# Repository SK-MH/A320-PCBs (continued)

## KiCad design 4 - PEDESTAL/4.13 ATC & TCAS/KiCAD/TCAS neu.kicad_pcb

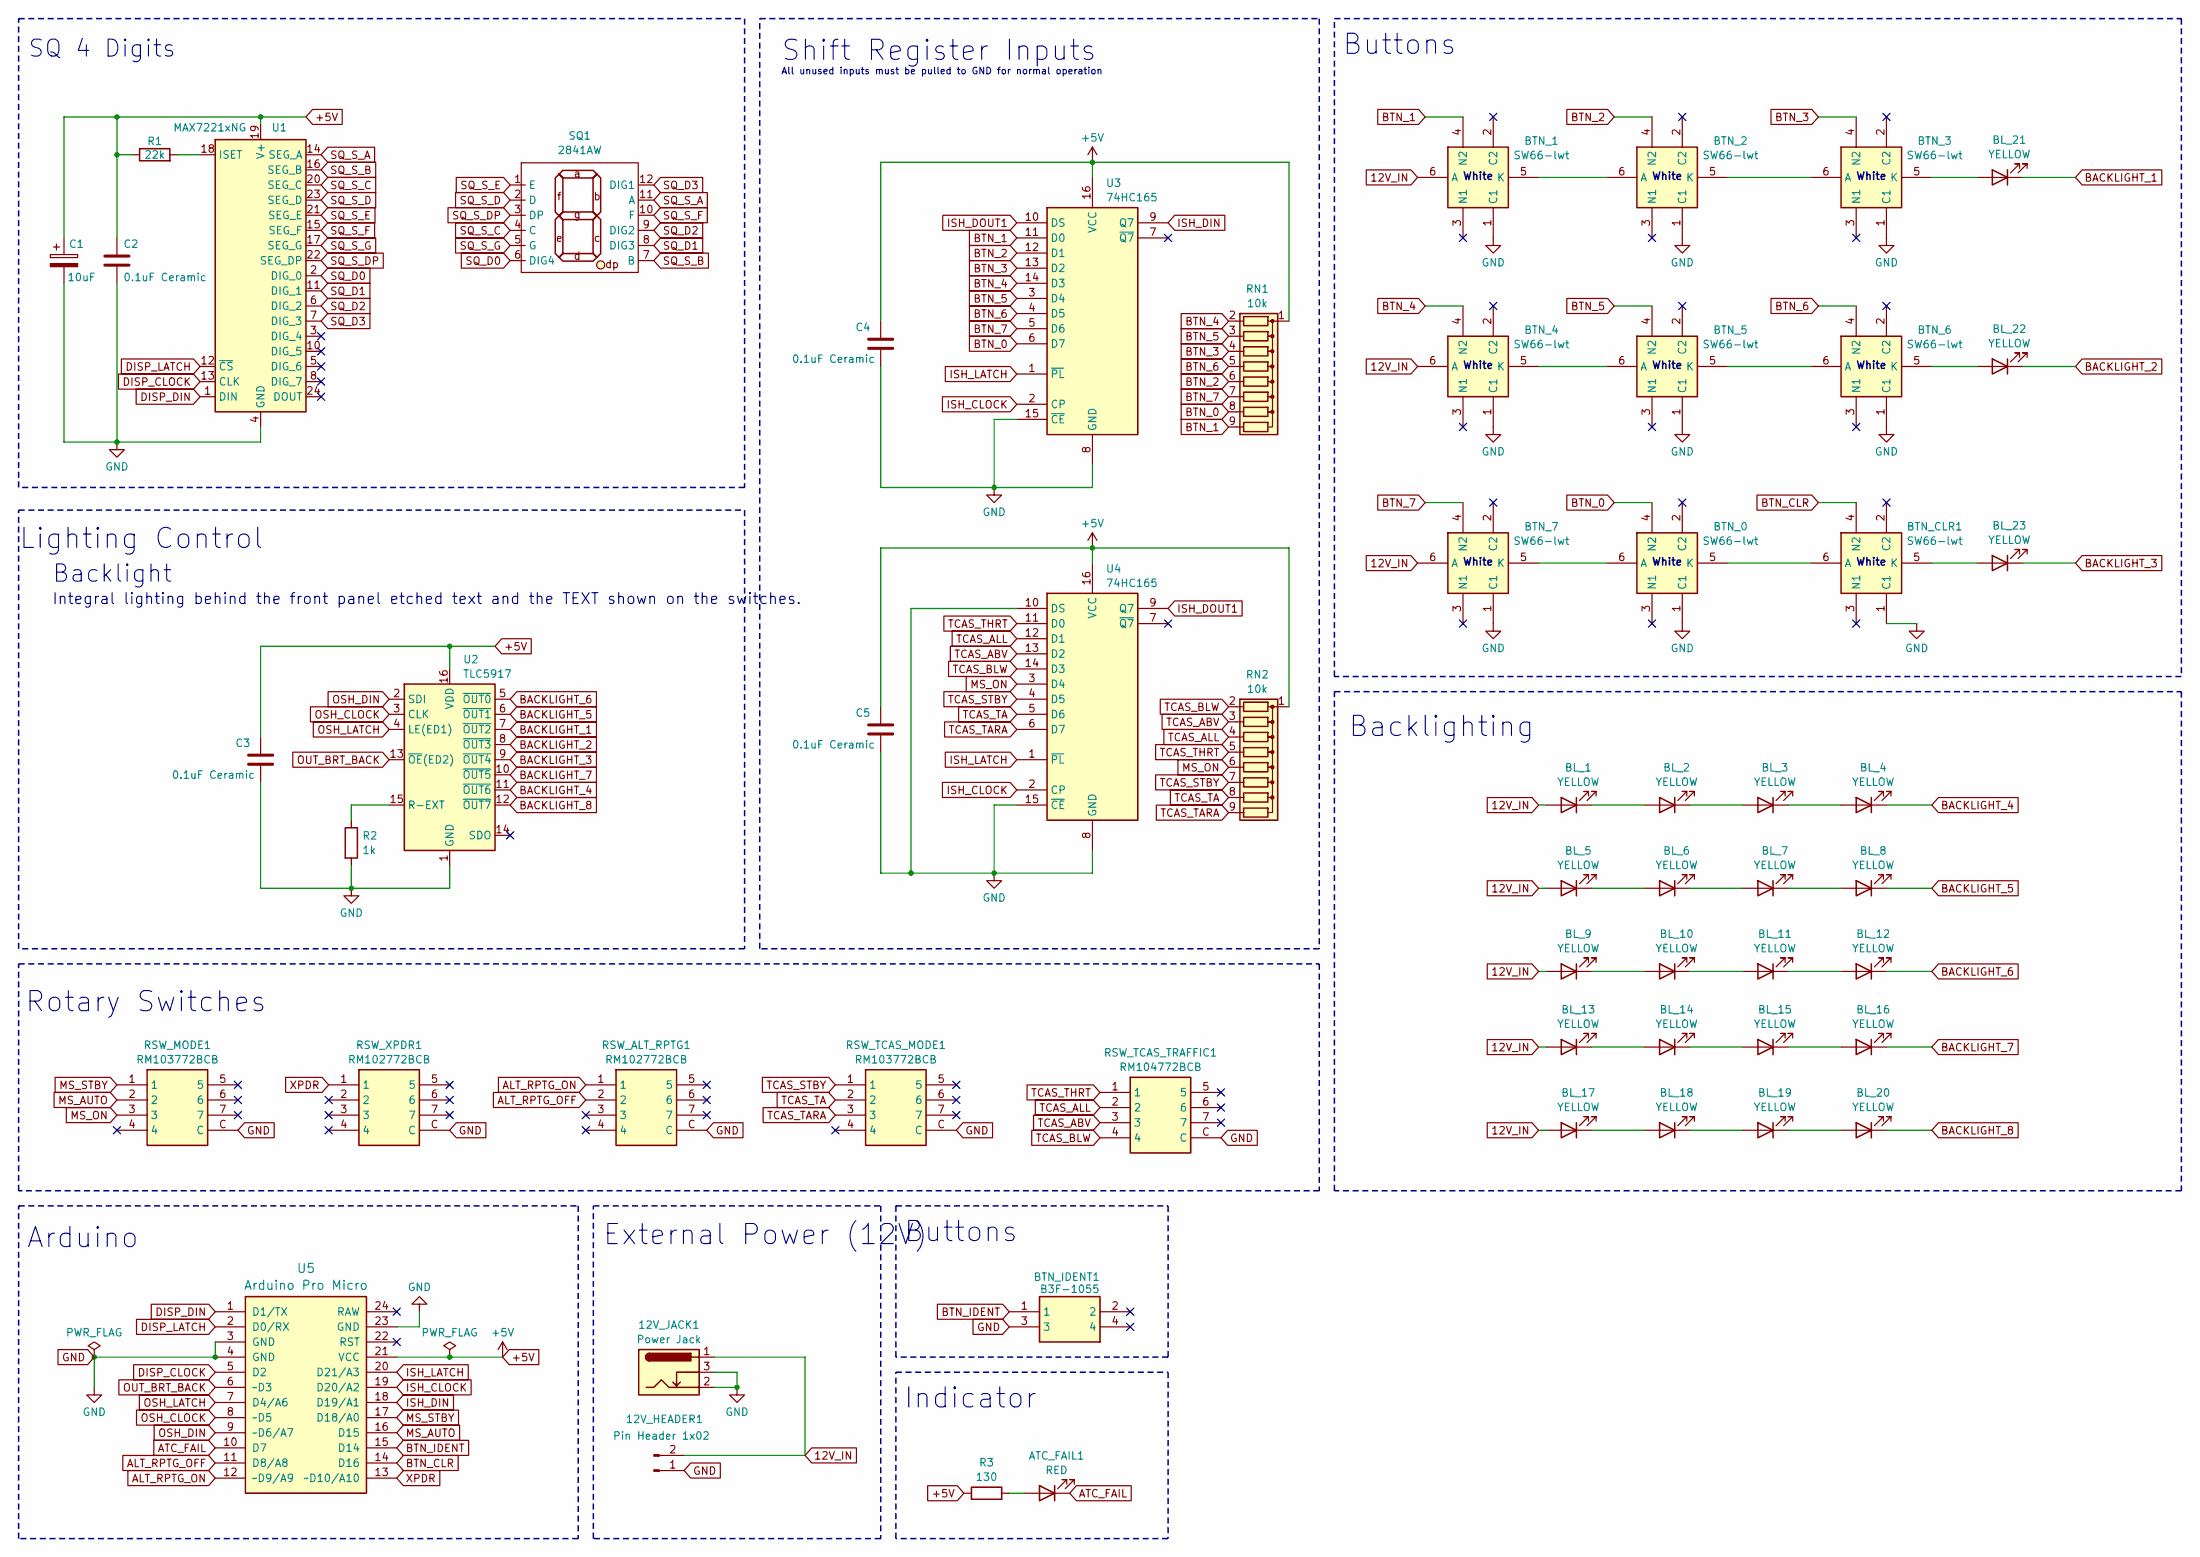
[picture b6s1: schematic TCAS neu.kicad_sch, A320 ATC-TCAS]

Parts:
12V_HEADER1: Pin Header 1x02; JST_EH_B2B-EH-A_1x02_P2.50mm_Vertical
12V_JACK1: Power Jack; BarrelJack_Horizontal
ATC_FAIL1: RED; LED_D3.0mm
BL_1, BL_2, BL_3, BL_4, BL_5, BL_6, BL_7, BL_8, BL_9, BL_10, BL_11, BL_12, BL_13, BL_14, BL_15, BL_16, BL_17, BL_18, BL_19, BL_20, BL_21, BL_22, BL_23: YELLOW; LED_D3.0mm
BTN_0, BTN_1, BTN_2, BTN_3, BTN_4, BTN_5, BTN_6, BTN_7: SW66-lwt
BTN_CLR1: SW66-lwt
BTN_IDENT1: B3F-1055; B3F1000; Mouser Part Number 653-B3F-1055
C1: 10uF; CP_Radial_D4.0mm_P1.50mm
C2, C3, C4, C5: 0.1uF Ceramic; C_Disc_D3.0mm_W1.6mm_P2.50mm
R1: 22k; R_Axial_DIN0204_L3.6mm_D1.6mm_P7.62mm_Horizontal
R2: 1k; R_Axial_DIN0204_L3.6mm_D1.6mm_P7.62mm_Horizontal
R3: 130; R_Axial_DIN0204_L3.6mm_D1.6mm_P7.62mm_Horizontal
RN1, RN2: 10k; R_Array_SIP9
RSW_ALT_RPTG1: RM102772BCB; myRM103772BCB; Mouser Part Number 611-RM103772BCB
RSW_MODE1: RM103772BCB; myRM103772BCB; Mouser Part Number 611-RM103772BCB
RSW_TCAS_MODE1: RM103772BCB; myRM103772BCB; Mouser Part Number 611-RM103772BCB
RSW_TCAS_TRAFFIC1: RM104772BCB; myRM103772BCB; Mouser Part Number 611-RM103772BCB
RSW_XPDR1: RM102772BCB; myRM103772BCB; Mouser Part Number 611-RM103772BCB
SQ1: 2841AW
U1: MAX7221xNG; DIP-24_W7.62mm
U2: TLC5917; DIP-16_W7.62mm
U3, U4: 74HC165; DIP-16_W7.62mm
U5: Arduino Pro Micro; Sparkfun_Pro_Micro

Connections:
12V_IN: 12V_HEADER1.2, 12V_JACK1.1, BL_1.2 (A), BL_5.2 (A), BL_9.2 (A), BL_13.2 (A), BL_17.2 (A), BTN_1.6 (A), BTN_4.6 (A), BTN_7.6 (A)
+5V: C1.1, C2.1, C3.1, C4.1, C5.1, R1.1, R3.1, RN1.1 (common), RN2.1 (common), U1.19 (V+), U2.16 (VDD), U3.16 (VCC), U4.16 (VCC), U5.21 (VCC)
ALT_RPTG_OFF: RSW_ALT_RPTG1.2, U5.11 (D8/A8)
ALT_RPTG_ON: RSW_ALT_RPTG1.1, U5.12 (~D9/A9)
ATC_FAIL: ATC_FAIL1.1 (K), U5.10 (D7)
BACKLIGHT_1: BL_21.1 (K), U2.7 (~OUT2)
BACKLIGHT_2: BL_22.1 (K), U2.8 (~OUT3)
BACKLIGHT_3: BL_23.1 (K), U2.9 (~OUT4)
BACKLIGHT_4: BL_4.1 (K), U2.11 (~OUT6)
BACKLIGHT_5: BL_8.1 (K), U2.6 (~OUT1)
BACKLIGHT_6: BL_12.1 (K), U2.5 (~OUT0)
BACKLIGHT_7: BL_16.1 (K), U2.10 (~OUT5)
BACKLIGHT_8: BL_20.1 (K), U2.12 (~OUT7)
BTN_0: BTN_0.4 (N2), RN1.8 (R7), U3.6 (D7)
BTN_1: BTN_1.4 (N2), RN1.9 (R8), U3.11 (D0)
BTN_2: BTN_2.4 (N2), RN1.6 (R5), U3.12 (D1)
BTN_3: BTN_3.4 (N2), RN1.4 (R3), U3.13 (D2)
BTN_4: BTN_4.4 (N2), RN1.2 (R1), U3.14 (D3)
BTN_5: BTN_5.4 (N2), RN1.3 (R2), U3.3 (D4)
BTN_6: BTN_6.4 (N2), RN1.5 (R4), U3.4 (D5)
BTN_7: BTN_7.4 (N2), RN1.7 (R6), U3.5 (D6)
BTN_CLR: BTN_CLR1.4 (N2), U5.14 (D16)
BTN_IDENT: BTN_IDENT1.1, U5.15 (D14)
DISP_CLOCK: U1.13 (CLK), U5.5 (D2)
DISP_DIN: U1.1 (DIN), U5.1 (D1/TX)
DISP_LATCH: U1.12 (~CS), U5.2 (D0/RX)
GND: 12V_HEADER1.1, 12V_JACK1.2, 12V_JACK1.3, BTN_0.1 (C1), BTN_1.1 (C1), BTN_2.1 (C1), BTN_3.1 (C1), BTN_4.1 (C1), BTN_5.1 (C1), BTN_6.1 (C1), BTN_7.1 (C1), BTN_CLR1.1 (C1), BTN_IDENT1.3, C1.2, C2.2, C3.2, C4.2, C5.2, R2.2, RSW_ALT_RPTG1.C, RSW_MODE1.C, RSW_TCAS_MODE1.C, RSW_TCAS_TRAFFIC1.C, RSW_XPDR1.C, U1.4 (GND), U1.9 (GND), U2.1 (GND), U3.8 (GND), U3.15 (~CE), U4.8 (GND), U4.10 (DS), U4.15 (~CE), U5.3 (GND), U5.4 (GND), U5.23 (GND)
ISH_CLOCK: U3.2 (CP), U4.2 (CP), U5.19 (D20/A2)
ISH_DIN: U3.9 (Q7), U5.18 (D19/A1)
ISH_DOUT1: U3.10 (DS), U4.9 (Q7)
ISH_LATCH: U3.1 (~PL), U4.1 (~PL), U5.20 (D21/A3)
MS_AUTO: RSW_MODE1.2, U5.16 (D15)
MS_ON: RN2.6 (R5), RSW_MODE1.3, U4.3 (D4)
MS_STBY: RSW_MODE1.1, U5.17 (D18/A0)
unnamed: ATC_FAIL1.2 (A), R3.2
unnamed: BL_1.1 (K), BL_2.2 (A)
unnamed: BL_2.1 (K), BL_3.2 (A)
unnamed: BL_3.1 (K), BL_4.2 (A)
unnamed: BL_5.1 (K), BL_6.2 (A)
unnamed: BL_6.1 (K), BL_7.2 (A)
unnamed: BL_7.1 (K), BL_8.2 (A)
unnamed: BL_9.1 (K), BL_10.2 (A)
unnamed: BL_10.1 (K), BL_11.2 (A)
unnamed: BL_11.1 (K), BL_12.2 (A)
unnamed: BL_13.1 (K), BL_14.2 (A)
unnamed: BL_14.1 (K), BL_15.2 (A)
unnamed: BL_15.1 (K), BL_16.2 (A)
unnamed: BL_17.1 (K), BL_18.2 (A)
unnamed: BL_18.1 (K), BL_19.2 (A)
unnamed: BL_19.1 (K), BL_20.2 (A)
unnamed: BL_21.2 (A), BTN_3.5 (K)
unnamed: BL_22.2 (A), BTN_6.5 (K)
unnamed: BL_23.2 (A), BTN_CLR1.5 (K)
unnamed: BTN_0.6 (A), BTN_7.5 (K)
unnamed: BTN_0.5 (K), BTN_CLR1.6 (A)
unnamed: BTN_1.5 (K), BTN_2.6 (A)
unnamed: BTN_2.5 (K), BTN_3.6 (A)
unnamed: BTN_4.5 (K), BTN_5.6 (A)
unnamed: BTN_5.5 (K), BTN_6.6 (A)
unnamed: R1.2, U1.18 (ISET)
unnamed: R2.1, U2.15 (R-EXT)
OSH_CLOCK: U2.3 (CLK), U5.8 (~D5)
OSH_DIN: U2.2 (SDI), U5.9 (~D6/A7)
OSH_LATCH: U2.4 (LE(ED1)), U5.7 (D4/A6)
OUT_BRT_BACK: U2.13 (~OE(ED2)), U5.6 (~D3)
SQ_D0: SQ1.6 (DIG4), U1.2 (DIG_0)
SQ_D1: SQ1.8 (DIG3), U1.11 (DIG_1)
SQ_D2: SQ1.9 (DIG2), U1.6 (DIG_2)
SQ_D3: SQ1.12 (DIG1), U1.7 (DIG_3)
SQ_S_A: SQ1.11 (A), U1.14 (SEG_A)
SQ_S_B: SQ1.7 (B), U1.16 (SEG_B)
SQ_S_C: SQ1.4 (C), U1.20 (SEG_C)
SQ_S_D: SQ1.2 (D), U1.23 (SEG_D)
SQ_S_DP: SQ1.3 (DP), U1.22 (SEG_DP)
SQ_S_E: SQ1.1 (E), U1.21 (SEG_E)
SQ_S_F: SQ1.10 (F), U1.15 (SEG_F)
SQ_S_G: SQ1.5 (G), U1.17 (SEG_G)
TCAS_ABV: RN2.3 (R2), RSW_TCAS_TRAFFIC1.3, U4.13 (D2)
TCAS_ALL: RN2.4 (R3), RSW_TCAS_TRAFFIC1.2, U4.12 (D1)
TCAS_BLW: RN2.2 (R1), RSW_TCAS_TRAFFIC1.4, U4.14 (D3)
TCAS_STBY: RN2.7 (R6), RSW_TCAS_MODE1.1, U4.4 (D5)
TCAS_TA: RN2.8 (R7), RSW_TCAS_MODE1.2, U4.5 (D6)
TCAS_TARA: RN2.9 (R8), RSW_TCAS_MODE1.3, U4.6 (D7)
TCAS_THRT: RN2.5 (R4), RSW_TCAS_TRAFFIC1.1, U4.11 (D0)
XPDR: RSW_XPDR1.1, U5.13 (~D10/A10)

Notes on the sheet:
White
Shift Register Inputs
Indicator
External Power (12V)
Integral lighting behind the front panel etched text and the TEXT shown on the switches.
Rotary Switches
SQ 4 Digits
All unused inputs must be pulled to GND for normal operation
Backlight
Buttons
Backlighting
Lighting Control
Arduino

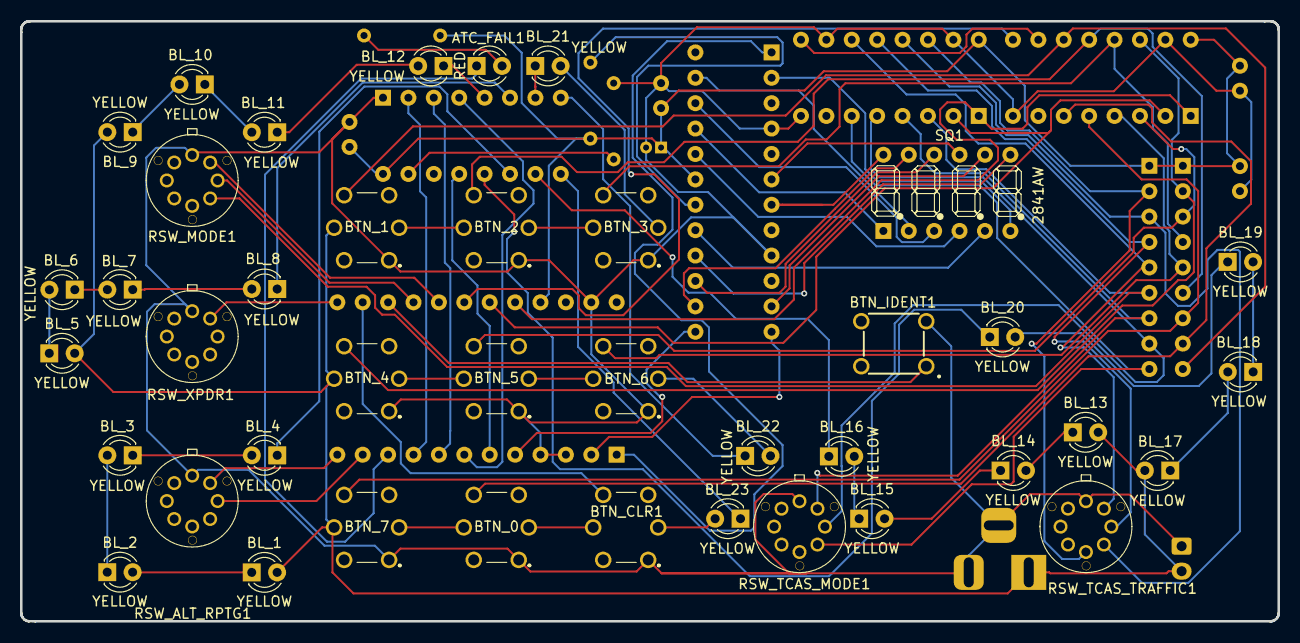
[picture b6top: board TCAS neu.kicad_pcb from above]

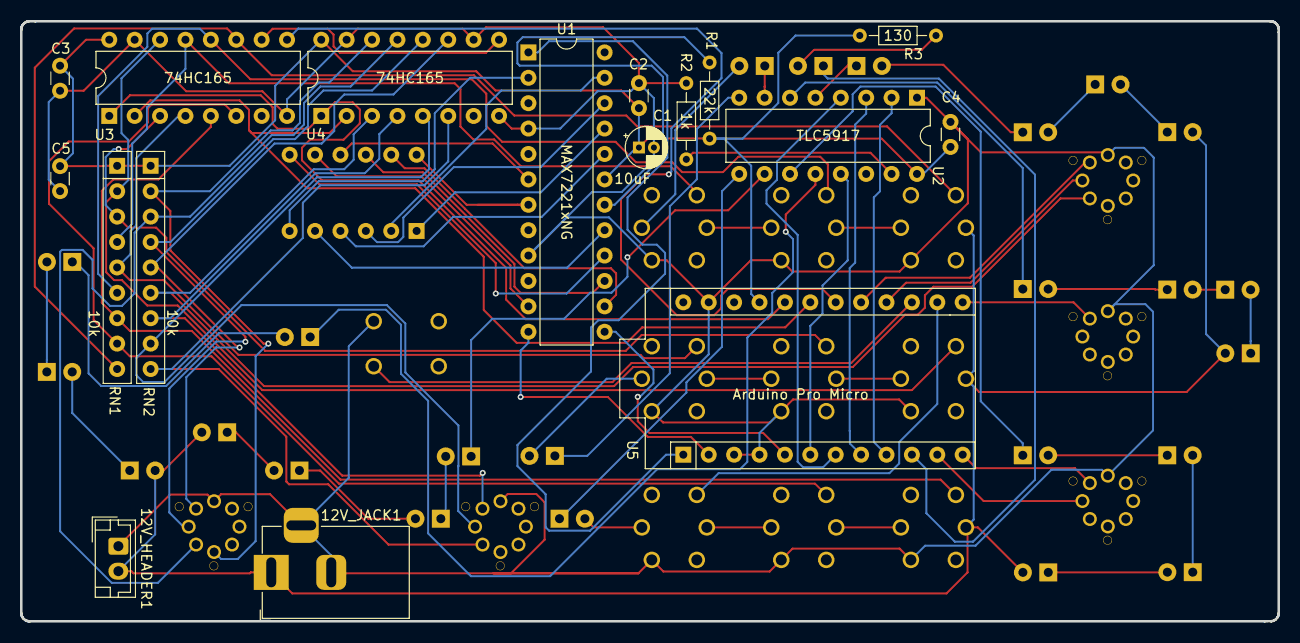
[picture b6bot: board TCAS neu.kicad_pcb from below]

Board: 2 copper layers, 125.8 x 60.0 mm, 57 parts (17 on the bottom side), 85 nets.

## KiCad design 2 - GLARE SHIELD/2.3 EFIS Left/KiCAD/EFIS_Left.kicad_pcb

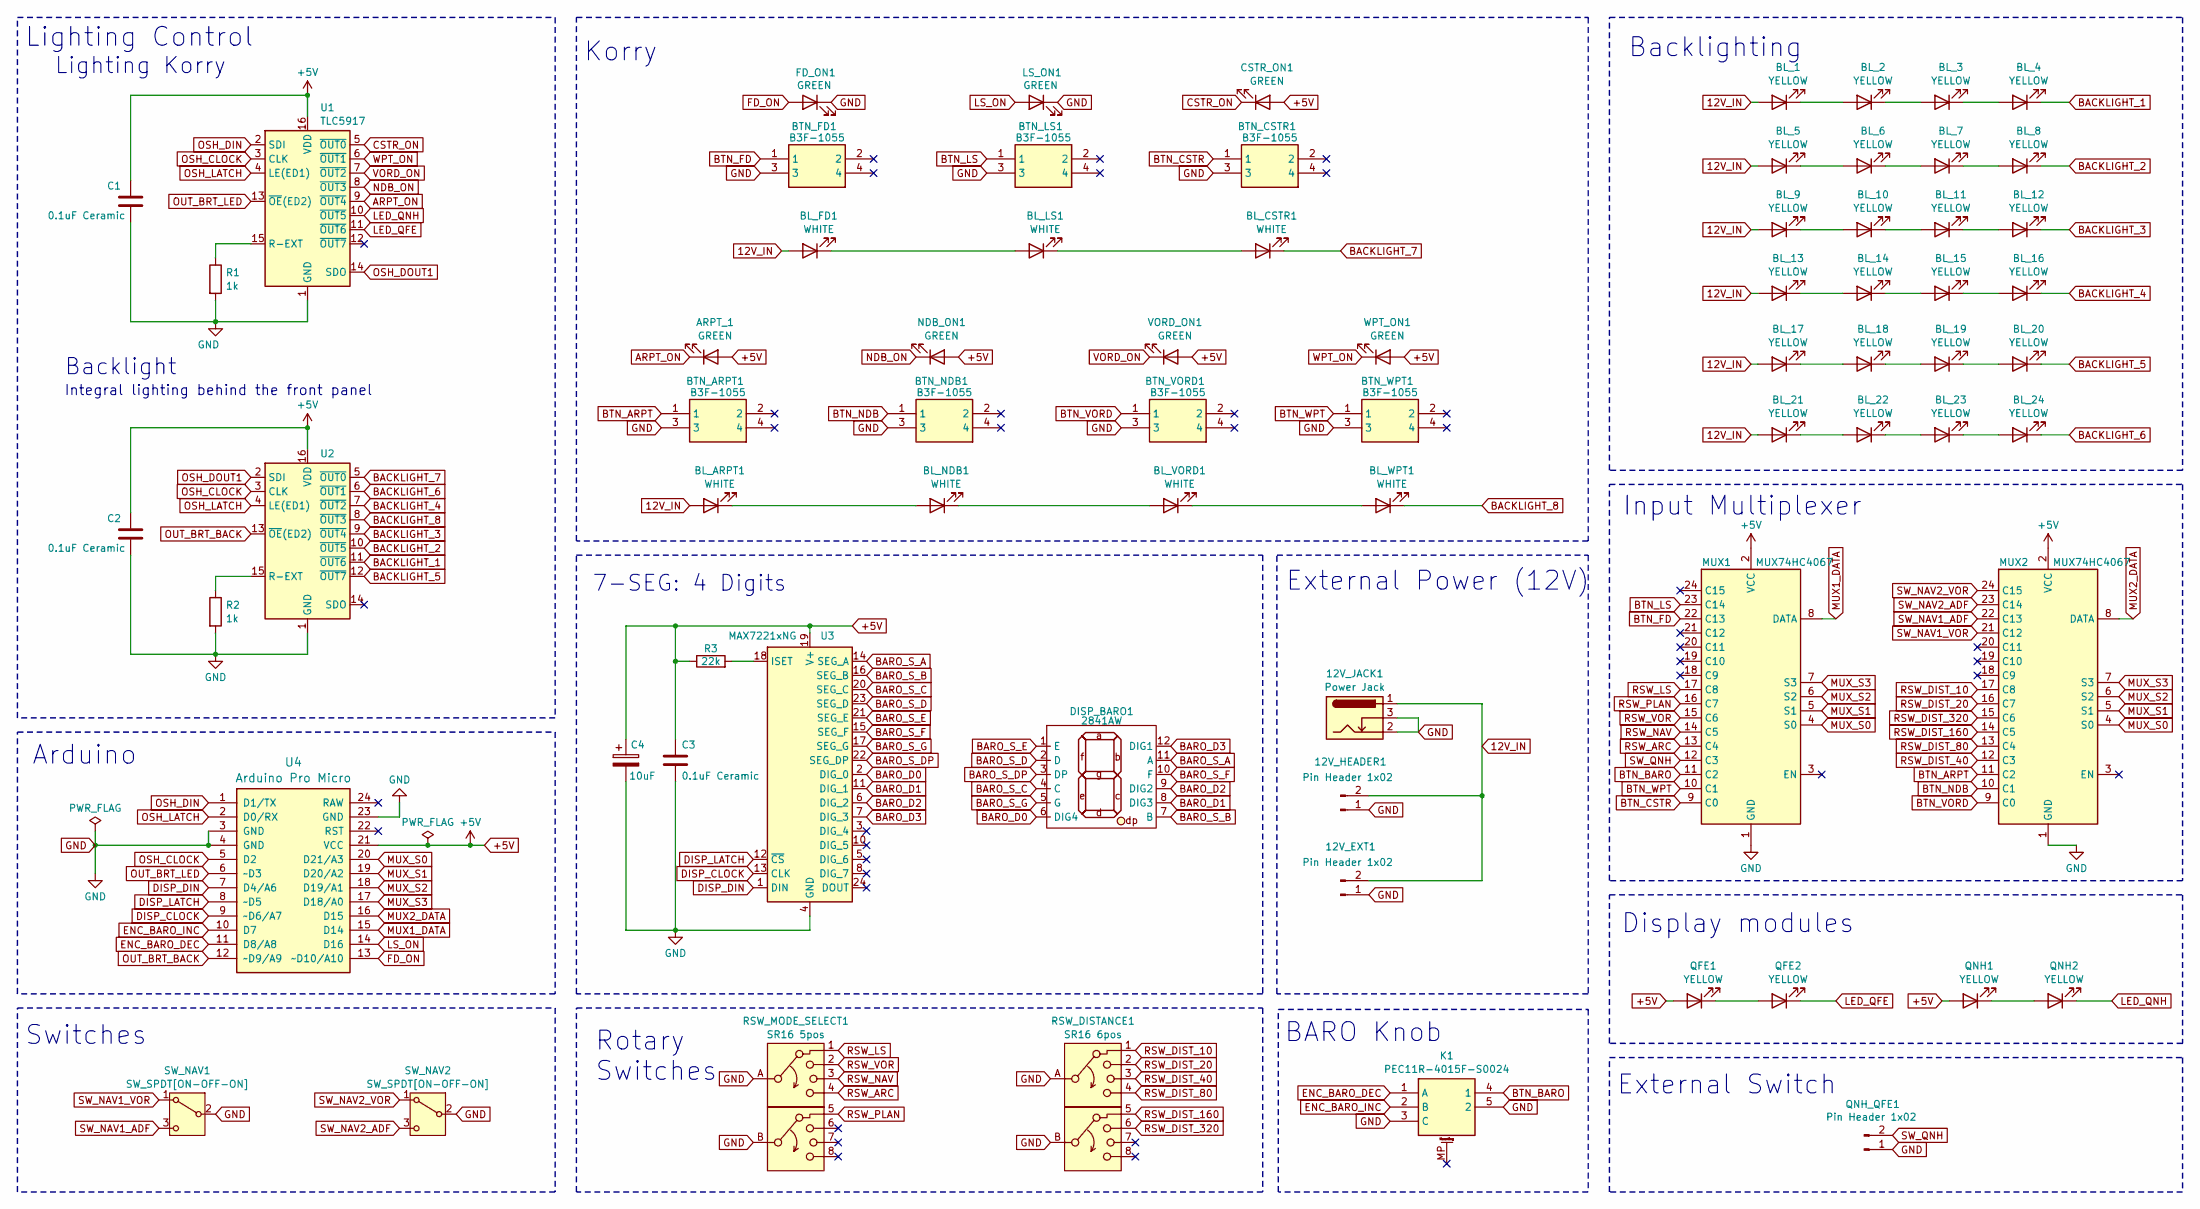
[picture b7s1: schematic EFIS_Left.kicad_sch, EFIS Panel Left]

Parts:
12V_EXT1, 12V_HEADER1: Pin Header 1x02; JST_EH_B2B-EH-A_1x02_P2.50mm_Vertical
12V_JACK1: Power Jack; BarrelJack_Horizontal
ARPT_1: GREEN; LED_D3.0mm
BL_1, BL_2, BL_3, BL_4, BL_5, BL_6, BL_7, BL_8, BL_9, BL_10, BL_11, BL_12, BL_13, BL_14, BL_15, BL_16, BL_17, BL_18, BL_19, BL_20, BL_21, BL_22, BL_23, BL_24: YELLOW; LED_D3.0mm
BL_ARPT1: WHITE; LED_D3.0mm
BL_CSTR1: WHITE; LED_D3.0mm
BL_FD1: WHITE; LED_D3.0mm
BL_LS1: WHITE; LED_D3.0mm
BL_NDB1: WHITE; LED_D3.0mm
BL_VORD1: WHITE; LED_D3.0mm
BL_WPT1: WHITE; LED_D3.0mm
BTN_ARPT1: B3F-1055; B3F1000; Mouser Part Number 653-B3F-1055
BTN_CSTR1: B3F-1055; B3F1000; Mouser Part Number 653-B3F-1055
BTN_FD1: B3F-1055; B3F1000; Mouser Part Number 653-B3F-1055
BTN_LS1: B3F-1055; B3F1000; Mouser Part Number 653-B3F-1055
BTN_NDB1: B3F-1055; B3F1000; Mouser Part Number 653-B3F-1055
BTN_VORD1: B3F-1055; B3F1000; Mouser Part Number 653-B3F-1055
BTN_WPT1: B3F-1055; B3F1000; Mouser Part Number 653-B3F-1055
C1, C2, C3: 0.1uF Ceramic; C_Disc_D3.0mm_W1.6mm_P2.50mm
C4: 10uF; CP_Radial_D4.0mm_P1.50mm
CSTR_ON1: GREEN; LED_D3.0mm
DISP_BARO1: 2841AW
FD_ON1: GREEN; LED_D3.0mm
K1: PEC11R-4015F-S0024; PEC12R-4XXXF-SXXXX_1; Mouser Part Number 652-PEC11R-4015F-S24
LS_ON1: GREEN; LED_D3.0mm
MUX1, MUX2: MUX74HC4067
NDB_ON1: GREEN; LED_D3.0mm
QFE1, QFE2: YELLOW; LED_D3.0mm
QNH1, QNH2: YELLOW; LED_D3.0mm
QNH_QFE1: Pin Header 1x02; JST_EH_B2B-EH-A_1x02_P2.50mm_Vertical
R1, R2: 1k; R_Axial_DIN0204_L3.6mm_D1.6mm_P7.62mm_Horizontal
R3: 22k; R_Axial_DIN0204_L3.6mm_D1.6mm_P7.62mm_Horizontal
RSW_DISTANCE1: SR16 6pos; SR16-AB
RSW_MODE_SELECT1: SR16 5pos; SR16-AB
SW_NAV1, SW_NAV2: SW_SPDT[ON-OFF-ON]; T80-Z1
U1, U2: TLC5917; DIP-16_W7.62mm
U3: MAX7221xNG; DIP-24_W7.62mm
U4: Arduino Pro Micro; Sparkfun_Pro_Micro
VORD_ON1: GREEN; LED_D3.0mm
WPT_ON1: GREEN; LED_D3.0mm

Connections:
12V_IN: 12V_EXT1.2, 12V_HEADER1.2, 12V_JACK1.1, BL_1.2 (A), BL_5.2 (A), BL_9.2 (A), BL_13.2 (A), BL_17.2 (A), BL_21.2 (A), BL_ARPT1.2 (A), BL_FD1.2 (A)
+5V: ARPT_1.2 (A), C1.1, C2.1, C3.1, C4.1, CSTR_ON1.2 (A), MUX1.2 (VCC), MUX2.2 (VCC), NDB_ON1.2 (A), QFE1.2 (A), QNH1.2 (A), R3.1, U1.16 (VDD), U2.16 (VDD), U3.19 (V+), U4.21 (VCC), VORD_ON1.2 (A), WPT_ON1.2 (A)
ARPT_ON: ARPT_1.1 (K), U1.9 (~OUT4)
BACKLIGHT_1: BL_4.1 (K), U2.11 (~OUT6)
BACKLIGHT_2: BL_8.1 (K), U2.10 (~OUT5)
BACKLIGHT_3: BL_12.1 (K), U2.9 (~OUT4)
BACKLIGHT_4: BL_16.1 (K), U2.7 (~OUT2)
BACKLIGHT_5: BL_20.1 (K), U2.12 (~OUT7)
BACKLIGHT_6: BL_24.1 (K), U2.6 (~OUT1)
BACKLIGHT_7: BL_CSTR1.1 (K), U2.5 (~OUT0)
BACKLIGHT_8: BL_WPT1.1 (K), U2.8 (~OUT3)
BARO_D0: DISP_BARO1.6 (DIG4), U3.2 (DIG_0)
BARO_D1: DISP_BARO1.8 (DIG3), U3.11 (DIG_1)
BARO_D2: DISP_BARO1.9 (DIG2), U3.6 (DIG_2)
BARO_D3: DISP_BARO1.12 (DIG1), U3.7 (DIG_3)
BARO_S_A: DISP_BARO1.11 (A), U3.14 (SEG_A)
BARO_S_B: DISP_BARO1.7 (B), U3.16 (SEG_B)
BARO_S_C: DISP_BARO1.4 (C), U3.20 (SEG_C)
BARO_S_D: DISP_BARO1.2 (D), U3.23 (SEG_D)
BARO_S_DP: DISP_BARO1.3 (DP), U3.22 (SEG_DP)
BARO_S_E: DISP_BARO1.1 (E), U3.21 (SEG_E)
BARO_S_F: DISP_BARO1.10 (F), U3.15 (SEG_F)
BARO_S_G: DISP_BARO1.5 (G), U3.17 (SEG_G)
BTN_ARPT: BTN_ARPT1.1, MUX2.11 (C2)
BTN_BARO: K1.4 (1), MUX1.11 (C2)
BTN_CSTR: BTN_CSTR1.1, MUX1.9 (C0)
BTN_FD: BTN_FD1.1, MUX1.22 (C13)
BTN_LS: BTN_LS1.1, MUX1.23 (C14)
BTN_NDB: BTN_NDB1.1, MUX2.10 (C1)
BTN_VORD: BTN_VORD1.1, MUX2.9 (C0)
BTN_WPT: BTN_WPT1.1, MUX1.10 (C1)
CSTR_ON: CSTR_ON1.1 (K), U1.5 (~OUT0)
DISP_CLOCK: U3.13 (CLK), U4.9 (~D6/A7)
DISP_DIN: U3.1 (DIN), U4.7 (D4/A6)
DISP_LATCH: U3.12 (~CS), U4.8 (~D5)
ENC_BARO_DEC: K1.1 (A), U4.11 (D8/A8)
ENC_BARO_INC: K1.2 (B), U4.10 (D7)
FD_ON: FD_ON1.2 (A), U4.13 (~D10/A10)
GND: 12V_EXT1.1, 12V_HEADER1.1, 12V_JACK1.2, 12V_JACK1.3, BTN_ARPT1.3, BTN_CSTR1.3, BTN_FD1.3, BTN_LS1.3, BTN_NDB1.3, BTN_VORD1.3, BTN_WPT1.3, C1.2, C2.2, C3.2, C4.2, FD_ON1.1 (K), K1.3 (C), K1.5 (2), LS_ON1.1 (K), MUX1.1 (GND), MUX2.1 (GND), QNH_QFE1.1, R1.2, R2.2, RSW_DISTANCE1.A, RSW_DISTANCE1.B, RSW_MODE_SELECT1.A, RSW_MODE_SELECT1.B, SW_NAV1.2 (B), SW_NAV2.2 (B), U1.1 (GND), U2.1 (GND), U3.4 (GND), U3.9 (GND), U4.3 (GND), U4.4 (GND), U4.23 (GND)
LED_QFE: QFE2.1 (K), U1.11 (~OUT6)
LED_QNH: QNH2.1 (K), U1.10 (~OUT5)
LS_ON: LS_ON1.2 (A), U4.14 (D16)
MUX1_DATA: MUX1.8 (DATA), U4.15 (D14)
MUX2_DATA: MUX2.8 (DATA), U4.16 (D15)
MUX_S0: MUX1.4 (S0), MUX2.4 (S0), U4.20 (D21/A3)
MUX_S1: MUX1.5 (S1), MUX2.5 (S1), U4.19 (D20/A2)
MUX_S2: MUX1.6 (S2), MUX2.6 (S2), U4.18 (D19/A1)
MUX_S3: MUX1.7 (S3), MUX2.7 (S3), U4.17 (D18/A0)
NDB_ON: NDB_ON1.1 (K), U1.8 (~OUT3)
unnamed: BL_1.1 (K), BL_2.2 (A)
unnamed: BL_2.1 (K), BL_3.2 (A)
unnamed: BL_3.1 (K), BL_4.2 (A)
unnamed: BL_5.1 (K), BL_6.2 (A)
unnamed: BL_6.1 (K), BL_7.2 (A)
unnamed: BL_7.1 (K), BL_8.2 (A)
unnamed: BL_9.1 (K), BL_10.2 (A)
unnamed: BL_10.1 (K), BL_11.2 (A)
unnamed: BL_11.1 (K), BL_12.2 (A)
unnamed: BL_13.1 (K), BL_14.2 (A)
unnamed: BL_14.1 (K), BL_15.2 (A)
unnamed: BL_15.1 (K), BL_16.2 (A)
unnamed: BL_17.1 (K), BL_18.2 (A)
unnamed: BL_18.1 (K), BL_19.2 (A)
unnamed: BL_19.1 (K), BL_20.2 (A)
unnamed: BL_21.1 (K), BL_22.2 (A)
unnamed: BL_22.1 (K), BL_23.2 (A)
unnamed: BL_23.1 (K), BL_24.2 (A)
unnamed: BL_ARPT1.1 (K), BL_NDB1.2 (A)
unnamed: BL_CSTR1.2 (A), BL_LS1.1 (K)
unnamed: BL_FD1.1 (K), BL_LS1.2 (A)
unnamed: BL_NDB1.1 (K), BL_VORD1.2 (A)
unnamed: BL_VORD1.1 (K), BL_WPT1.2 (A)
unnamed: QFE1.1 (K), QFE2.2 (A)
unnamed: QNH1.1 (K), QNH2.2 (A)
unnamed: R1.1, U1.15 (R-EXT)
unnamed: R2.1, U2.15 (R-EXT)
unnamed: R3.2, U3.18 (ISET)
OSH_CLOCK: U1.3 (CLK), U2.3 (CLK), U4.5 (D2)
OSH_DIN: U1.2 (SDI), U4.1 (D1/TX)
OSH_DOUT1: U1.14 (SDO), U2.2 (SDI)
OSH_LATCH: U1.4 (LE(ED1)), U2.4 (LE(ED1)), U4.2 (D0/RX)
OUT_BRT_BACK: U2.13 (~OE(ED2)), U4.12 (~D9/A9)
OUT_BRT_LED: U1.13 (~OE(ED2)), U4.6 (~D3)
RSW_ARC: MUX1.13 (C4), RSW_MODE_SELECT1.4
RSW_DIST_10: MUX2.17 (C8), RSW_DISTANCE1.1
RSW_DIST_20: MUX2.16 (C7), RSW_DISTANCE1.2
RSW_DIST_40: MUX2.12 (C3), RSW_DISTANCE1.3
RSW_DIST_80: MUX2.13 (C4), RSW_DISTANCE1.4
RSW_DIST_160: MUX2.14 (C5), RSW_DISTANCE1.5
RSW_DIST_320: MUX2.15 (C6), RSW_DISTANCE1.6
RSW_LS: MUX1.17 (C8), RSW_MODE_SELECT1.1
RSW_NAV: MUX1.14 (C5), RSW_MODE_SELECT1.3
RSW_PLAN: MUX1.16 (C7), RSW_MODE_SELECT1.5
RSW_VOR: MUX1.15 (C6), RSW_MODE_SELECT1.2
SW_NAV1_ADF: MUX2.22 (C13), SW_NAV1.3 (C)
SW_NAV1_VOR: MUX2.21 (C12), SW_NAV1.1 (A)
SW_NAV2_ADF: MUX2.23 (C14), SW_NAV2.3 (C)
SW_NAV2_VOR: MUX2.24 (C15), SW_NAV2.1 (A)
SW_QNH: MUX1.12 (C3), QNH_QFE1.2
VORD_ON: U1.7 (~OUT2), VORD_ON1.1 (K)
WPT_ON: U1.6 (~OUT1), WPT_ON1.1 (K)

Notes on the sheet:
Switches
Backlighting
7-SEG: 4 Digits
Arduino
BARO Knob
Display modules
Rotary Switches
Korry
External Switch
Input Multiplexer
External Power (12V)
Lighting Korry
Lighting Control
Integral lighting behind the front panel
Backlight

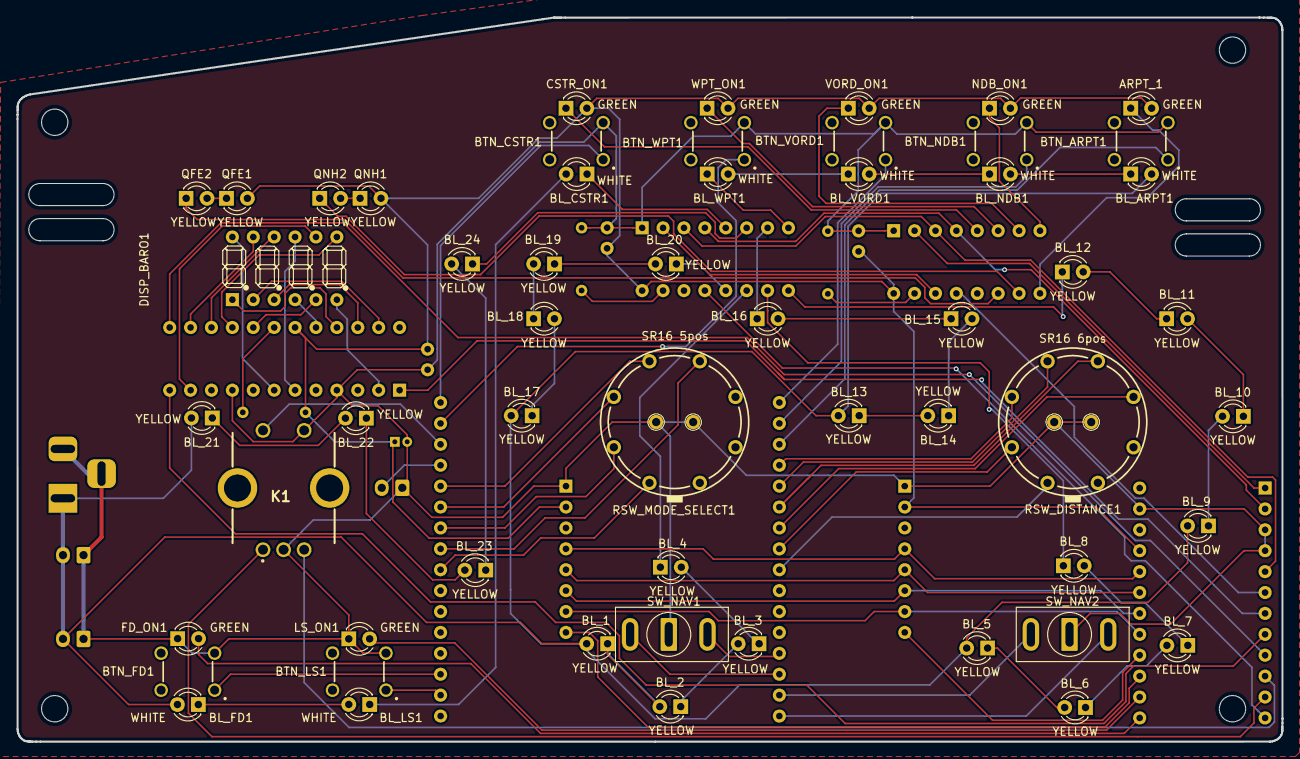
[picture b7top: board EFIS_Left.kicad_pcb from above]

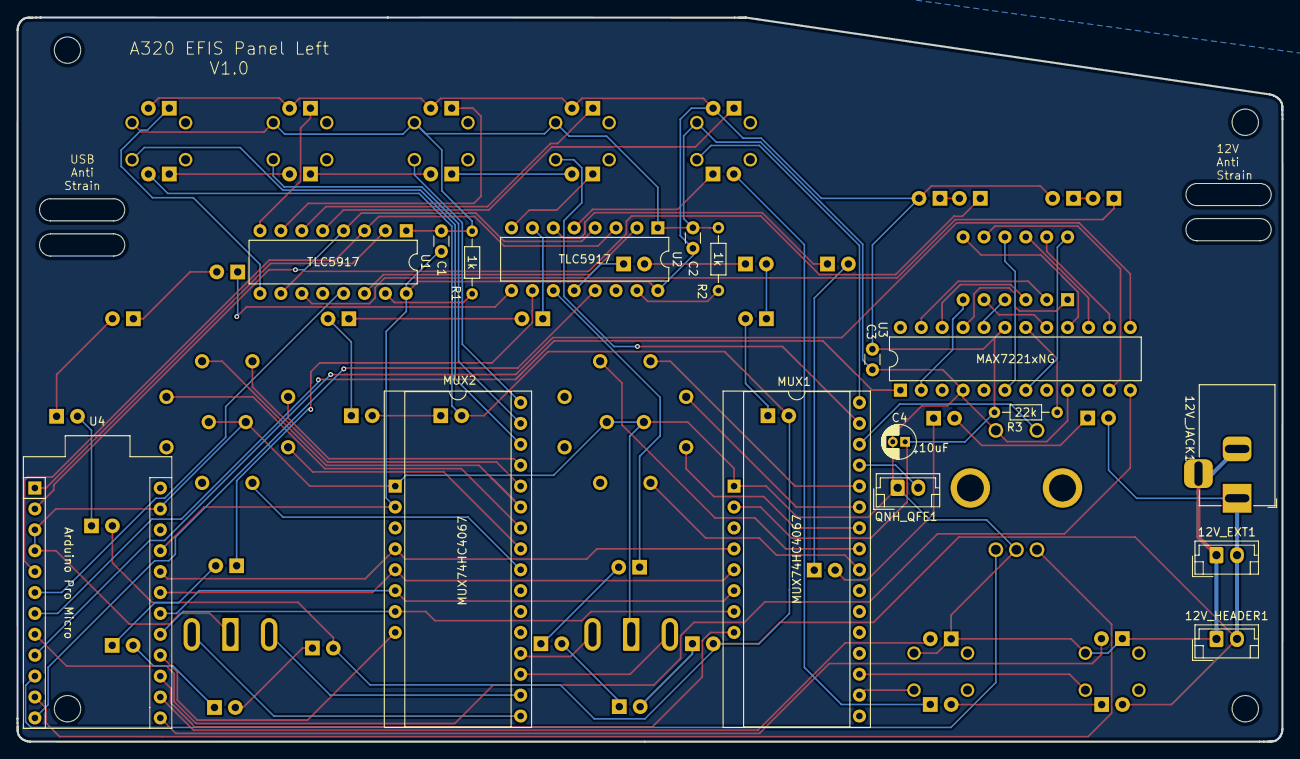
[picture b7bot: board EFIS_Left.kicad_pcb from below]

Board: 2 copper layers, 153.7 x 88.0 mm, 72 parts (17 on the bottom side), 101 nets.

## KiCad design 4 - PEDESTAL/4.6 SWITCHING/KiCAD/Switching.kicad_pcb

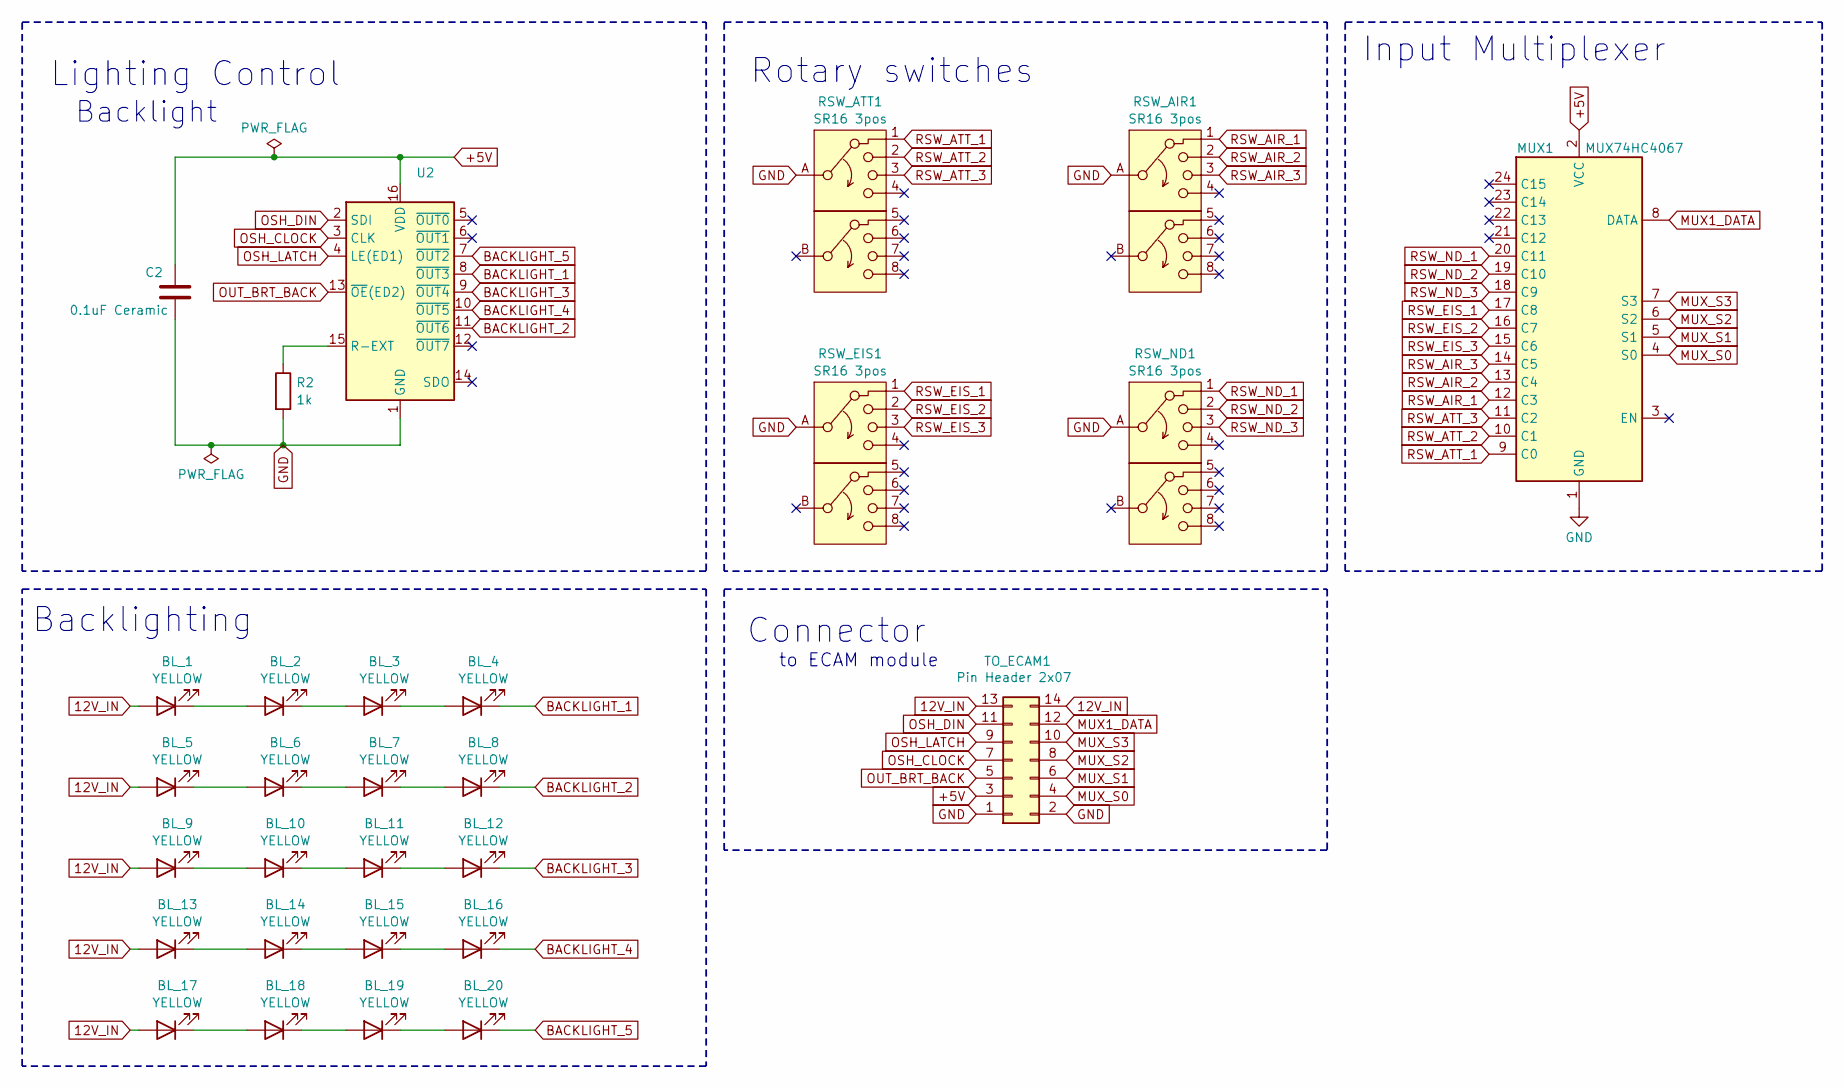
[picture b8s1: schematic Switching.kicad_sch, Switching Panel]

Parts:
BL_1, BL_2, BL_3, BL_4, BL_5, BL_6, BL_7, BL_8, BL_9, BL_10, BL_11, BL_12, BL_13, BL_14, BL_15, BL_16, BL_17, BL_18, BL_19, BL_20: YELLOW; LED_D3.0mm
C2: 0.1uF Ceramic; C_Disc_D3.0mm_W1.6mm_P2.50mm
MUX1: MUX74HC4067
R2: 1k; R_Axial_DIN0204_L3.6mm_D1.6mm_P5.08mm_Horizontal
RSW_AIR1: SR16 3pos; SR16-AB
RSW_ATT1: SR16 3pos; SR16-AB
RSW_EIS1: SR16 3pos; SR16-AB
RSW_ND1: SR16 3pos; SR16-AB
TO_ECAM1: Pin Header 2x07; IDC-Header_2x07_P2.54mm_Vertical
U2: TLC5917; DIP-16_W7.62mm

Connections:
12V_IN: BL_1.2 (A), BL_5.2 (A), BL_9.2 (A), BL_13.2 (A), BL_17.2 (A), TO_ECAM1.13, TO_ECAM1.14
+5V: C2.1, MUX1.2 (VCC), TO_ECAM1.3, U2.16 (VDD)
BACKLIGHT_1: BL_4.1 (K), U2.8 (~OUT3)
BACKLIGHT_2: BL_8.1 (K), U2.11 (~OUT6)
BACKLIGHT_3: BL_12.1 (K), U2.9 (~OUT4)
BACKLIGHT_4: BL_16.1 (K), U2.10 (~OUT5)
BACKLIGHT_5: BL_20.1 (K), U2.7 (~OUT2)
GND: C2.2, MUX1.1 (GND), R2.2, RSW_AIR1.A, RSW_ATT1.A, RSW_EIS1.A, RSW_ND1.A, TO_ECAM1.1, TO_ECAM1.2, U2.1 (GND)
MUX1_DATA: MUX1.8 (DATA), TO_ECAM1.12
MUX_S0: MUX1.4 (S0), TO_ECAM1.4
MUX_S1: MUX1.5 (S1), TO_ECAM1.6
MUX_S2: MUX1.6 (S2), TO_ECAM1.8
MUX_S3: MUX1.7 (S3), TO_ECAM1.10
unnamed: BL_1.1 (K), BL_2.2 (A)
unnamed: BL_2.1 (K), BL_3.2 (A)
unnamed: BL_3.1 (K), BL_4.2 (A)
unnamed: BL_5.1 (K), BL_6.2 (A)
unnamed: BL_6.1 (K), BL_7.2 (A)
unnamed: BL_7.1 (K), BL_8.2 (A)
unnamed: BL_9.1 (K), BL_10.2 (A)
unnamed: BL_10.1 (K), BL_11.2 (A)
unnamed: BL_11.1 (K), BL_12.2 (A)
unnamed: BL_13.1 (K), BL_14.2 (A)
unnamed: BL_14.1 (K), BL_15.2 (A)
unnamed: BL_15.1 (K), BL_16.2 (A)
unnamed: BL_17.1 (K), BL_18.2 (A)
unnamed: BL_18.1 (K), BL_19.2 (A)
unnamed: BL_19.1 (K), BL_20.2 (A)
unnamed: R2.1, U2.15 (R-EXT)
OSH_CLOCK: TO_ECAM1.7, U2.3 (CLK)
OSH_DIN: TO_ECAM1.11, U2.2 (SDI)
OSH_LATCH: TO_ECAM1.9, U2.4 (LE(ED1))
OUT_BRT_BACK: TO_ECAM1.5, U2.13 (~OE(ED2))
RSW_AIR_1: MUX1.12 (C3), RSW_AIR1.1
RSW_AIR_2: MUX1.13 (C4), RSW_AIR1.2
RSW_AIR_3: MUX1.14 (C5), RSW_AIR1.3
RSW_ATT_1: MUX1.9 (C0), RSW_ATT1.1
RSW_ATT_2: MUX1.10 (C1), RSW_ATT1.2
RSW_ATT_3: MUX1.11 (C2), RSW_ATT1.3
RSW_EIS_1: MUX1.17 (C8), RSW_EIS1.1
RSW_EIS_2: MUX1.16 (C7), RSW_EIS1.2
RSW_EIS_3: MUX1.15 (C6), RSW_EIS1.3
RSW_ND_1: MUX1.20 (C11), RSW_ND1.1
RSW_ND_2: MUX1.19 (C10), RSW_ND1.2
RSW_ND_3: MUX1.18 (C9), RSW_ND1.3

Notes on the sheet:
Connector
Rotary switches
Backlighting
Input Multiplexer
to ECAM module
Lighting Control
Backlight

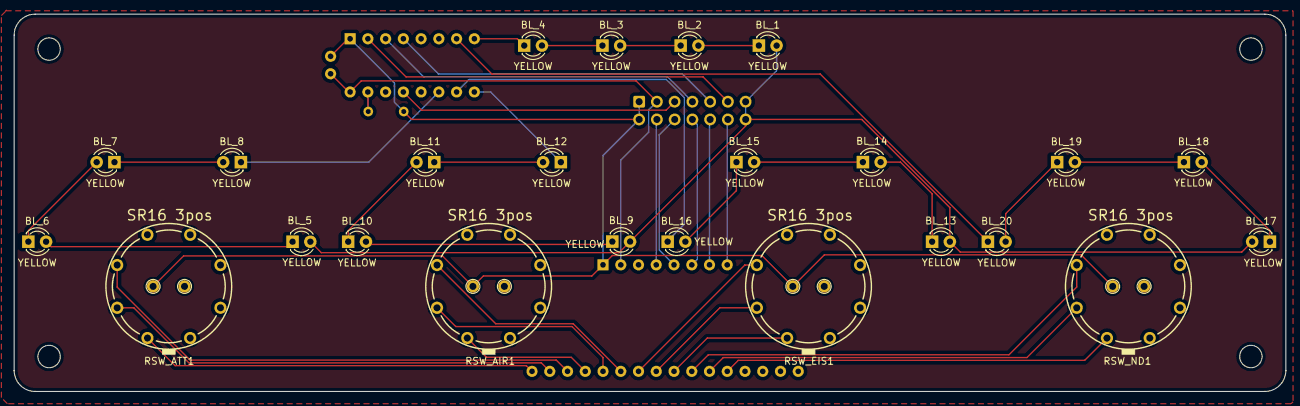
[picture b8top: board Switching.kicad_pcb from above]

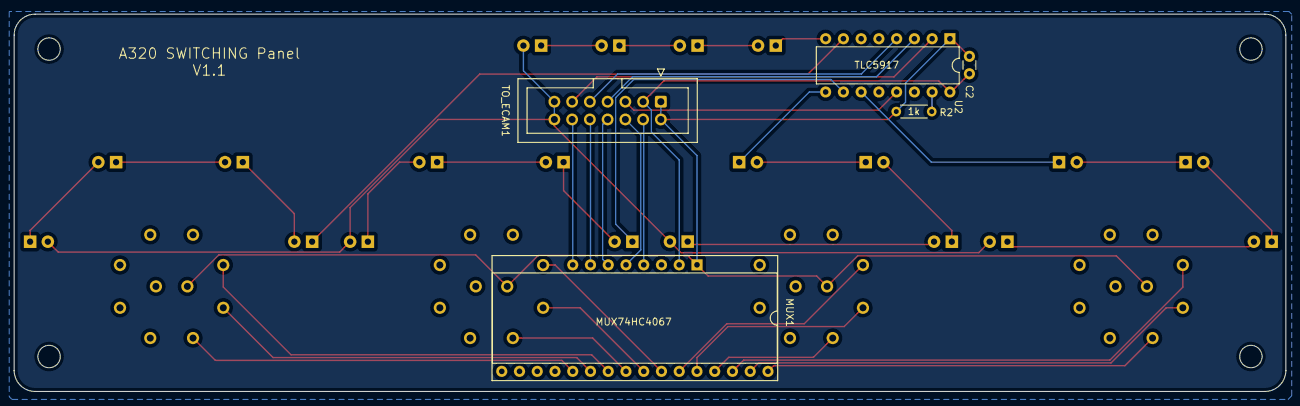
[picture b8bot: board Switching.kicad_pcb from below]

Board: 2 copper layers, 182.0 x 54.0 mm, 29 parts (5 on the bottom side), 45 nets.

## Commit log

2024-11-28 Initial load FLT_CTL
2024-11-28 Initial load FLT_CTL_FO
2024-11-28 Initial load ADIRS & Miscellaneous
2024-11-30 ADIRS connector initial load
2024-12-04 ToDo list added
2024-12-04 Files for CNC or Laser milling/engraving
    For engraving:
    In the lower left corner there is a marker.
    This points to the lower left corner on the plate.
    Use this for adjusting the CNC/Laser.
2025-01-06 Create 2 - GLARE SHIELD
2025-01-06 KiCAD files and other added
2025-01-06 gitignore changed
2025-01-06 Note changed
2025-01-06 More KiCAD files
2025-01-07 Enable JPG files
2025-01-07 ignore *.db
2025-01-07 JPG resized
2025-01-07 Docu started
